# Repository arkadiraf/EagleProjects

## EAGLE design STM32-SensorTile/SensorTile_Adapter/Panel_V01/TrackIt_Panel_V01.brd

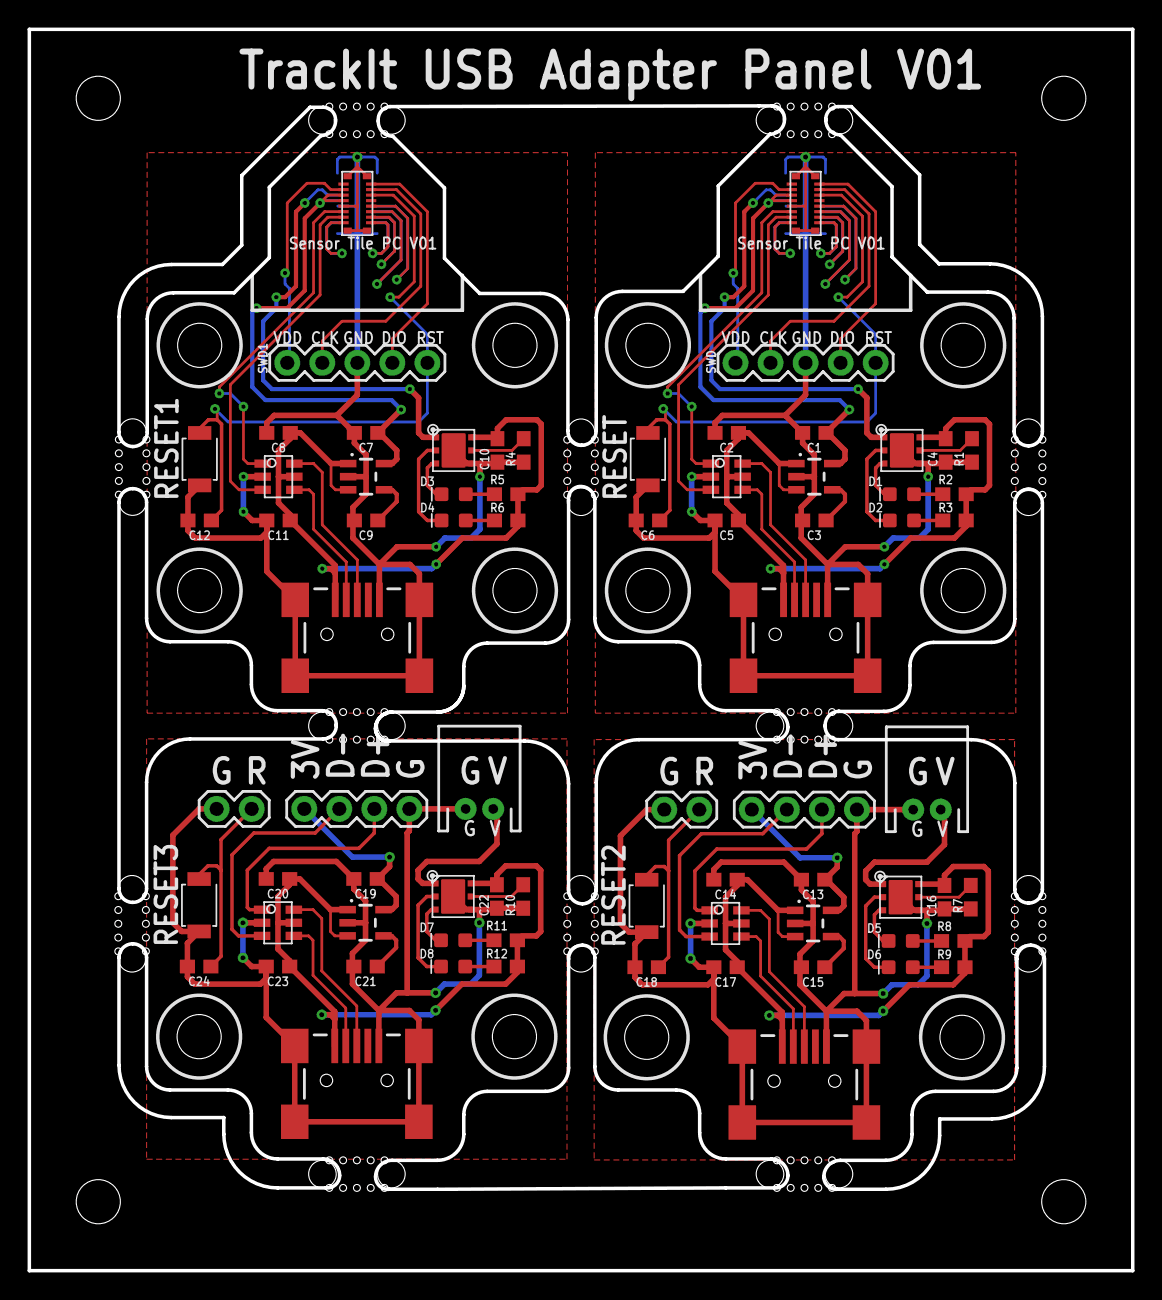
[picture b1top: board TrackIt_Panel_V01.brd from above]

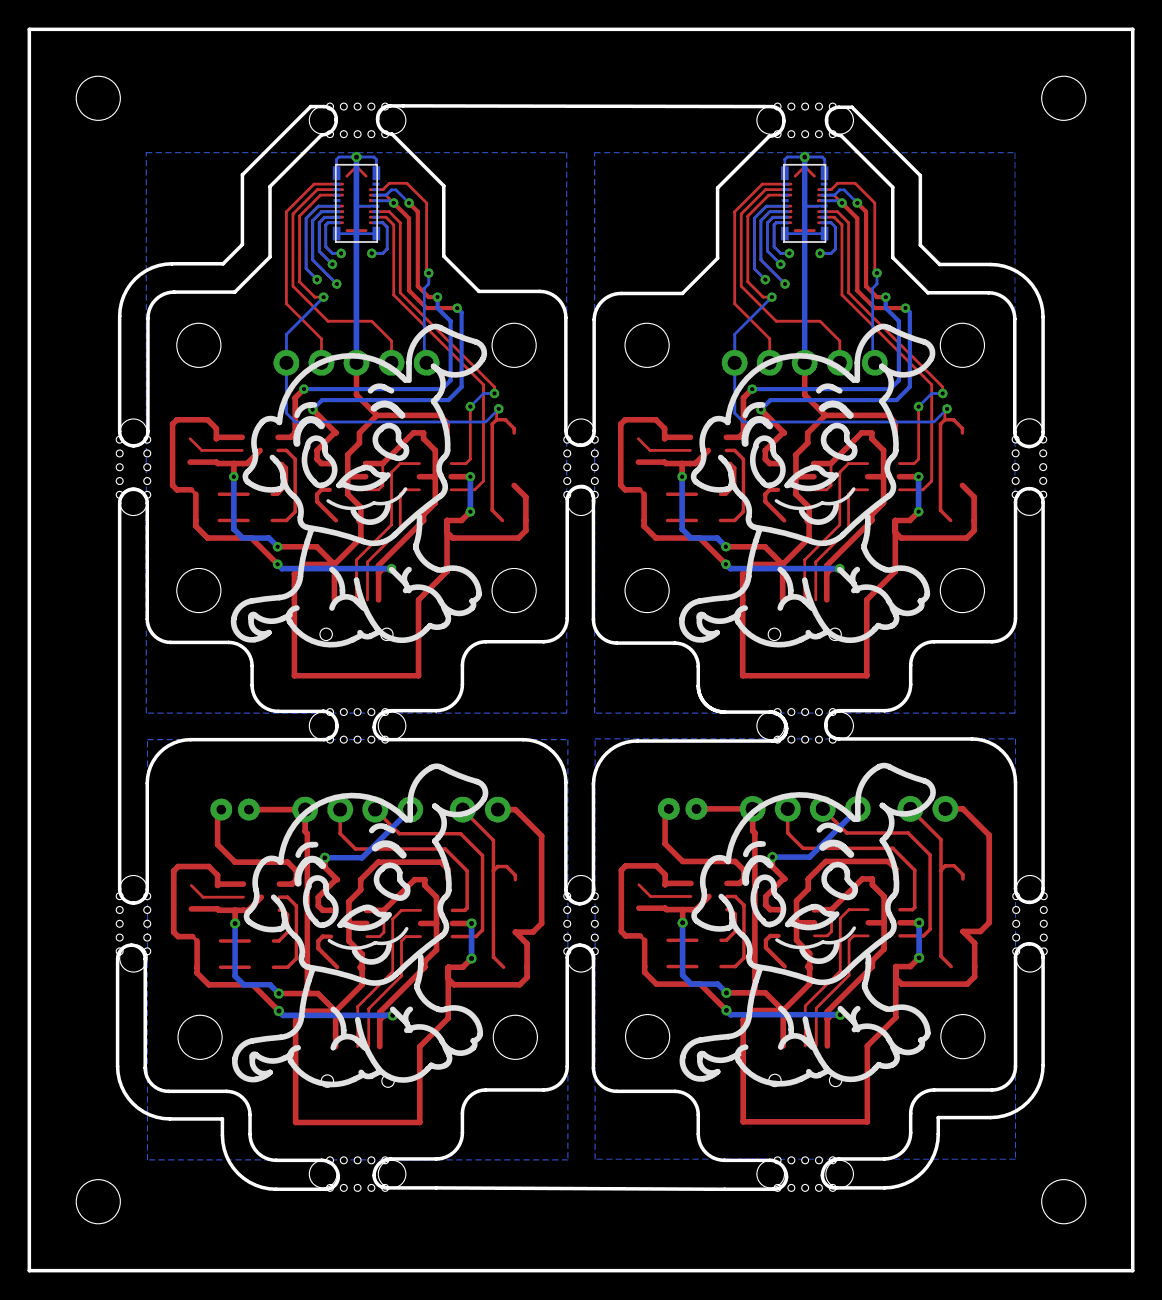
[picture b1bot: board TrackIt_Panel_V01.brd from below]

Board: 2 copper layers, 80.0 x 90.0 mm, 76 parts (2 on the bottom side), 76 nets.

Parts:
ADAPTER_BOARD, ADAPTER_BOARD1: BM10B(0.8)_BM10NB(0.8)-16DS-0.4V(51)
C1, C2, C4, C7, C8, C10, C13, C14, C16, C19, C20, C22: 1.0uF; 0603
C3, C9, C15, C21: 10nF; 0603
C5, C6, C11, C12, C17, C18, C23, C24: 0.1uF; 0603
D1, D3, D5, D7: BLUE; LED-0603
D2, D4, D6, D8: GREEN; LED-0603
J1, J2, J3, J7: USB_MINI-B_SMT; USB-MINIB
J4, J8: USB; 1X04
J5, J9: Bat; JST-2-PTH
J6, J10: Reset; 1X02
R1, R4, R7, R10: 47k; 0603
R2, R3, R5, R6, R8, R9, R11, R12: 1k; 0603
RESET, RESET1, RESET2, RESET3: B3U-3000PM; SW2-2.6-3.0X2.5X1.2+0.4MM
SENSOR_TILE, SENSOR_TILE1: BM10B(0.8)_BM10B(0.8)-16DP-0.4V(51)
SWD, SWD1: 1X05
U$1, U$3, U$7, U$10: LDK120M33R; SOT23-5
U$2, U$4, U$8, U$11: STBC08PMR; 6-DFN(3X3)
U$5, U$6, U$9, U$12: USBLC6; SOT23-6L

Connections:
3.3V: ADAPTER_BOARD.VUSB_3.3V, C1.1, SENSOR_TILE.VIN_2-5V, SENSOR_TILE.VUSB_3.3V, U$3.3V3&5
3.3V1: ADAPTER_BOARD1.VUSB_3.3V, C7.1, SENSOR_TILE1.VIN_2-5V, SENSOR_TILE1.VUSB_3.3V, U$1.3V3&5
3.3V2: C13.1, J4.4, U$7.3V3&5
3.3V3: C19.1, J8.4, U$10.3V3&5
GND: ADAPTER_BOARD.G$1, ADAPTER_BOARD.G$2, ADAPTER_BOARD.G$3, ADAPTER_BOARD.G$4, ADAPTER_BOARD.GND$1, C1.2, C2.2, C3.2, C4.2, C5.2, C6.2, J1.GND, J1.S1, J1.S2, J1.S3, J1.S4, R1.1, RESET.1, SENSOR_TILE.G$1, SENSOR_TILE.G$2, SENSOR_TILE.G$3, SENSOR_TILE.G$4, SENSOR_TILE.GND$1, SWD.3, U$3.GND$2, U$4.GND$4, U$4.PAD_GND$7, U$5.GND$2
GND1: ADAPTER_BOARD1.G$1, ADAPTER_BOARD1.G$2, ADAPTER_BOARD1.G$3, ADAPTER_BOARD1.G$4, ADAPTER_BOARD1.GND$1, C7.2, C8.2, C9.2, C10.2, C11.2, C12.2, J2.GND, J2.S1, J2.S2, J2.S3, J2.S4, R4.1, RESET1.1, SENSOR_TILE1.G$1, SENSOR_TILE1.G$2, SENSOR_TILE1.G$3, SENSOR_TILE1.G$4, SENSOR_TILE1.GND$1, SWD1.3, U$1.GND$2, U$2.GND$4, U$2.PAD_GND$7, U$6.GND$2
GND2: C13.2, C14.2, C15.2, C16.2, C17.2, C18.2, J3.GND, J3.S1, J3.S2, J3.S3, J3.S4, J4.1, J5.1, J6.1, R7.1, RESET2.1, U$7.GND$2, U$8.GND$4, U$8.PAD_GND$7, U$9.GND$2
GND3: C19.2, C20.2, C21.2, C22.2, C23.2, C24.2, J7.GND, J7.S1, J7.S2, J7.S3, J7.S4, J8.1, J9.1, J10.1, R10.1, RESET3.1, U$10.GND$2, U$11.GND$4, U$11.PAD_GND$7, U$12.GND$2
unnamed: R1.2, U$4.PROG$5
unnamed: J1.D+, U$5.D+OUT$1$6
unnamed: J1.D-, U$5.D-OUT$1$4
unnamed: D2.C, U$4.ON$2
unnamed: D1.C, U$4.CHRG$3
unnamed: C3.1, U$3.BYP$4
unnamed: D1.A, R2.1
unnamed: D2.A, R3.1
unnamed: ADAPTER_BOARD.GPIO2, SENSOR_TILE.GPIO2
unnamed: ADAPTER_BOARD.SPI_NSS, SENSOR_TILE.SPI_NSS
unnamed: ADAPTER_BOARD.SPI_MOSI, SENSOR_TILE.SPI_MOSI
unnamed: ADAPTER_BOARD.SPI_MISO, SENSOR_TILE.SPI_MISO
unnamed: J2.D+, U$6.D+OUT$1$6
unnamed: J2.D-, U$6.D-OUT$1$4
unnamed: C9.1, U$1.BYP$4
unnamed: R4.2, U$2.PROG$5
unnamed: D4.C, U$2.ON$2
unnamed: D3.C, U$2.CHRG$3
unnamed: D3.A, R5.1
unnamed: D4.A, R6.1
unnamed: ADAPTER_BOARD1.GPIO2, SENSOR_TILE1.GPIO2
unnamed: ADAPTER_BOARD1.SPI_NSS, SENSOR_TILE1.SPI_NSS
unnamed: ADAPTER_BOARD1.SPI_MOSI, SENSOR_TILE1.SPI_MOSI
unnamed: ADAPTER_BOARD1.SPI_MISO, SENSOR_TILE1.SPI_MISO
unnamed: J3.D+, U$9.D+OUT$1$6
unnamed: J3.D-, U$9.D-OUT$1$4
unnamed: C15.1, U$7.BYP$4
unnamed: R7.2, U$8.PROG$5
unnamed: D6.C, U$8.ON$2
unnamed: D5.C, U$8.CHRG$3
unnamed: D5.A, R8.1
unnamed: D6.A, R9.1
unnamed: J7.D+, U$12.D+OUT$1$6
unnamed: J7.D-, U$12.D-OUT$1$4
unnamed: C21.1, U$10.BYP$4
unnamed: R10.2, U$11.PROG$5
unnamed: D8.C, U$11.ON$2
unnamed: D7.C, U$11.CHRG$3
unnamed: D7.A, R11.1
unnamed: D8.A, R12.1
RESET: C6.1, RESET.2, SENSOR_TILE.NRST, SWD.5
RESET1: C12.1, RESET1.2, SENSOR_TILE1.NRST, SWD1.5
RESET2: C18.1, J6.2, RESET2.2
RESET3: C24.1, J10.2, RESET3.2
RX-USB_DP: SENSOR_TILE.RXD, U$5.D+IN$1
RX-USB_DP1: SENSOR_TILE1.RXD, U$6.D+IN$1
RX-USB_DP2: J4.2, U$9.D+IN$1
RX-USB_DP3: J8.2, U$12.D+IN$1
SPI_SCK: ADAPTER_BOARD.SPI_SCK, SENSOR_TILE.SPI_SCK
SPI_SCK1: ADAPTER_BOARD1.SPI_SCK, SENSOR_TILE1.SPI_SCK
SWDCLK: SENSOR_TILE.GPIO5, SWD.2
SWDCLK1: SENSOR_TILE1.GPIO5, SWD1.2
SWDIO: SENSOR_TILE.GPIO6, SWD.4
SWDIO1: SENSOR_TILE1.GPIO6, SWD1.4
TX-USB_DM: SENSOR_TILE.TXD, U$5.D-IN$3
TX-USB_DM1: SENSOR_TILE1.TXD, U$6.D-IN$3
TX-USB_DM2: J4.3, U$9.D-IN$3
TX-USB_DM3: J8.3, U$12.D-IN$3
VDD: SENSOR_TILE.VDD_1.8V, SWD.1
VDD1: SENSOR_TILE1.VDD_1.8V, SWD1.1
V_BATT: ADAPTER_BOARD.VIN_2-5V, U$4.BAT$1
V_BATT1: ADAPTER_BOARD1.VIN_2-5V, U$2.BAT$1
V_BATT2: J5.2, U$8.BAT$1
V_BATT3: J9.2, U$11.BAT$1
V_USB: C2.1, C4.1, C5.1, J1.VBUS, R2.2, R3.2, U$3.EN$3, U$3.VIN$1, U$4.VCC$6, U$5.VUSB$5
V_USB1: C8.1, C10.1, C11.1, J2.VBUS, R5.2, R6.2, U$1.EN$3, U$1.VIN$1, U$2.VCC$6, U$6.VUSB$5
V_USB2: C14.1, C16.1, C17.1, J3.VBUS, R8.2, R9.2, U$7.EN$3, U$7.VIN$1, U$8.VCC$6, U$9.VUSB$5
V_USB3: C20.1, C22.1, C23.1, J7.VBUS, R11.2, R12.2, U$10.EN$3, U$10.VIN$1, U$11.VCC$6, U$12.VUSB$5

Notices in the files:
parts and their libraries:
SparkFun-Capacitors: Licensing: Creative Commons ShareAlike 4.0 International - https://creativecommons.org/licenses/by-sa/4.0
